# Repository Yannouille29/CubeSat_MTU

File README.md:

# CubeSat MTU

This project is divided into two distinct stages. The first stage involved constructing a CubeSat using the information provided for the AMSAT CubeSatSim prototype, available at [CubeSatSim repository](https://github.com/alanbjohnston/CubeSatSim.git). We followed the steps outlined and replicated the foundation.

The second stage focused on enhancing the CubeSat in various ways to address a specific problem. In our case, we selected two distinct improvements. 

1. **Real-time Visualization of CubeSat in Space using Gyroscope:**
   We developed a 3D visualization of our CubeSat in real-time on a website. This visualization updates dynamically as the ground station receives information.

2. **Prototyping CubeSat Maneuverability using Reaction Wheels:**
   We restructured the CubeSat to accommodate two motors and new electronic circuit components. This enhancement allows the CubeSat to orient itself in space based on reaction wheel principles.

For each of these separate projects, you'll find dedicated folders containing all the necessary information. Additionally, we undertook a thorough analysis of the base code available for CubeSatSim to interact effectively with our enhancements. We've added comments to certain sections of code in the 'soft' directory for the purpose of understanding. It's important to note that these commented code sections have not been altered; they serve merely as tools for comprehension.

## Folder Structure

- **CubeSat_Troubleshooting:** Contains details related to the construction phase following the AMSAT prototype and the solutions to different problems.
- **Visualisation_Improvement:** Includes resources for the real-time 3D visualization of the CubeSat.
- **Reaction_Wheel_Improvement:** Encompasses information regarding the CubeSat's ability to orient itself using reaction wheels.
- **Soft:** Holds the original base code with additional comments for understanding purposes.
- **Web_Serveur:** Contains all the files necessary to visualize various web pages related to the Cubesat, including the work done by other group members.

Please refer to individual folders for specific details and resources related to each stage of the project.

## Important Note

The commented sections in the 'soft' directory serve as aids for understanding the base code and should not be modified. They are solely intended to facilitate comprehension.

## Contributors

- HUGUET Yann(https://github.com/Yannouille29)

Feel free to reach out to us for any inquiries or clarifications regarding this project.

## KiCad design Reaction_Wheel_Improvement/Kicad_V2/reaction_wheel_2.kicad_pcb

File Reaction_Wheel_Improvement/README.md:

# CubeSat Reaction Wheel Project

This repository contains all the essential elements created for the CubeSat Reaction Wheel project.

## Contents

- **3D_Simulation**: This directory contains all the Solidwork files updated specifically for the project. It includes the necessary files for the 3D simulation and modeling related to the CubeSat Reaction Wheel.

- **Arduino**: The Arduino directory houses the code essential for the SparkFun Arduino to operate within the Reaction Wheel project. 

- **KiCad**: This directory comprises the KiCad files, notably the "Kicad_V2" folder. It contains the electronic schema of the project's prototype and offers a potential version that can be translated into a PCB design, taking into account the components used.

## Usage

### 3D_Simulation

This directory includes Solidwork files that are crucial for 3D modeling. To utilize these files:

1. Ensure you have Solidwork installed on your system or another 3D visualisation tool.
2. Open the files using Solidwork to view the 3D model.

### Arduino

The Arduino directory holds the necessary code for the SparkFun Arduino to function within the Reaction Wheel project. Follow these steps:

1. Upload the code to your SparkFun Arduino board.
2. Ensure the connections are set up as specified in the documentation or comments within the code.

### KiCad

In this directory, particularly in the "Kicad_V2" folder, you'll find electronic schemas for the project's prototype and a potential PCB design. To use:

1. Open KiCad and load the schematic files for review or modification.
2. For PCB creation, follow the provided instructions or guidelines for creating a printed circuit board based on the schematic.

## Additional Notes

Please refer to individual directories for specific instructions, codes, or diagrams related to their respective components of the CubeSat Reaction Wheel project.

For questions or inquiries, feel free to contact [Yann HUGUET].

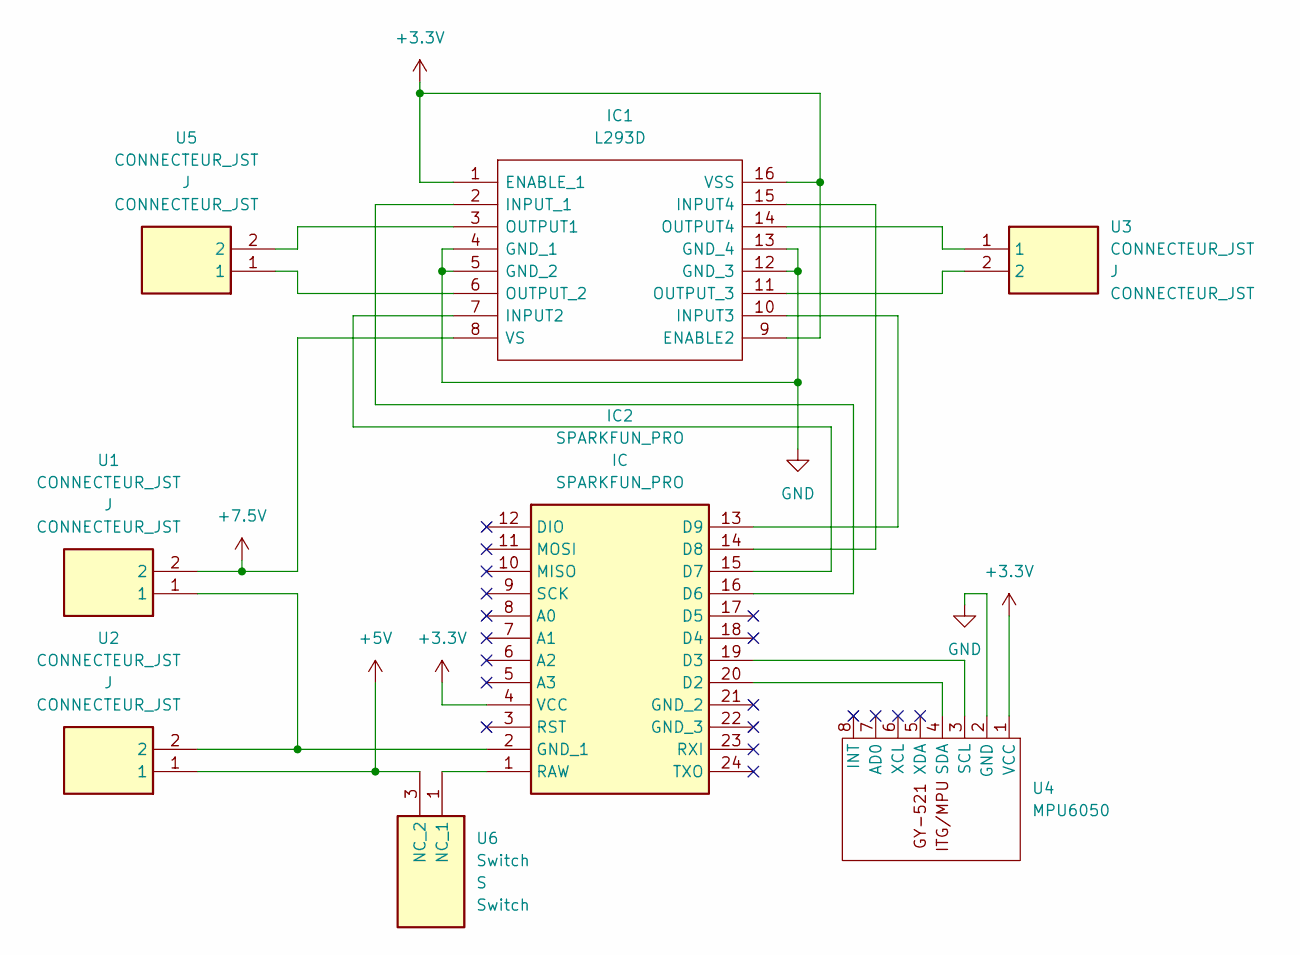
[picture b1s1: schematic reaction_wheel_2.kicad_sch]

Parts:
IC1: L293D; DIP880W50P254L2000H510Q16N; Manufacturer_Part_Number L293D; Mouser Part Number 511-L293D
IC2: SPARKFUN_PRO; DEV12587; Manufacturer_Part_Number DEV-12587; Mouser Part Number 474-DEV-12587
U1, U2, U3, U5: CONNECTEUR_JST; SHDR2W50P0X200_1X2_590X450X600P; Manufacturer_Part_Number B2B-PH-K-S(LF)(SN)
U4: MPU6050
U6: Switch; Manufacturer_Part_Number A11HP; Mouser Part Number 633-A11HP

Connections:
+3.3V: IC1.1 (ENABLE_1), IC1.9 (ENABLE2), IC1.16 (VSS), IC2.4 (VCC), U4.1 (VCC)
+5V: U2.1, U6.3 (NC_2)
+7.5V: IC1.8 (VS), U1.2
GND: IC1.4 (GND_1), IC1.5 (GND_2), IC1.12 (GND_3), IC1.13 (GND_4), U4.2 (GND)
unnamed: IC1.2 (INPUT_1), IC2.16 (D6)
unnamed: IC1.3 (OUTPUT1), U5.2
unnamed: IC1.6 (OUTPUT_2), U5.1
unnamed: IC1.7 (INPUT2), IC2.15 (D7)
unnamed: IC1.10 (INPUT3), IC2.13 (D9)
unnamed: IC1.11 (OUTPUT_3), U3.2
unnamed: IC1.14 (OUTPUT4), U3.1
unnamed: IC1.15 (INPUT4), IC2.14 (D8)
unnamed: IC2.19 (D3), U4.3 (SCL)
unnamed: IC2.2 (GND_1), U1.1, U2.2
unnamed: IC2.20 (D2), U4.4 (SDA)
unnamed: IC2.1 (RAW), U6.1 (NC_1)

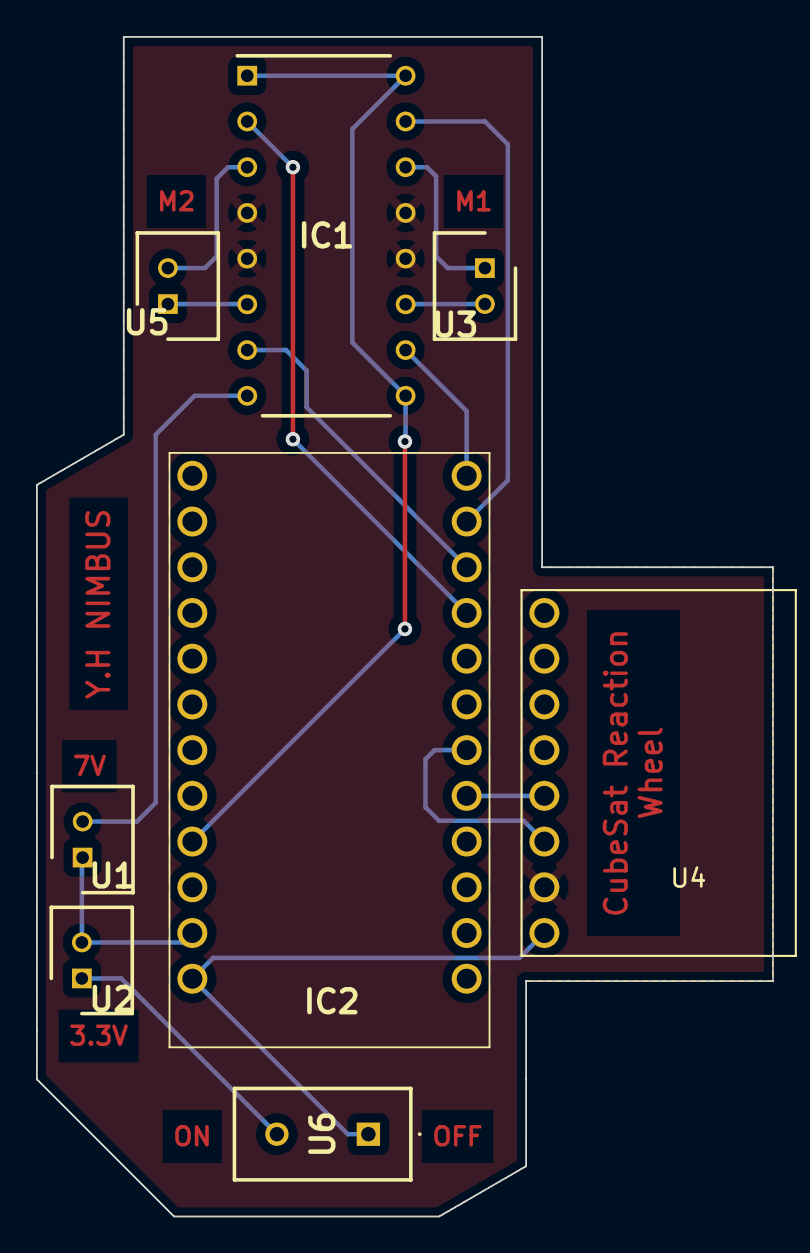
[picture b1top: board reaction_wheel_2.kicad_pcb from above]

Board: 2 copper layers, 40.9 x 65.5 mm, 8 parts (0 on the bottom side), 16 nets.

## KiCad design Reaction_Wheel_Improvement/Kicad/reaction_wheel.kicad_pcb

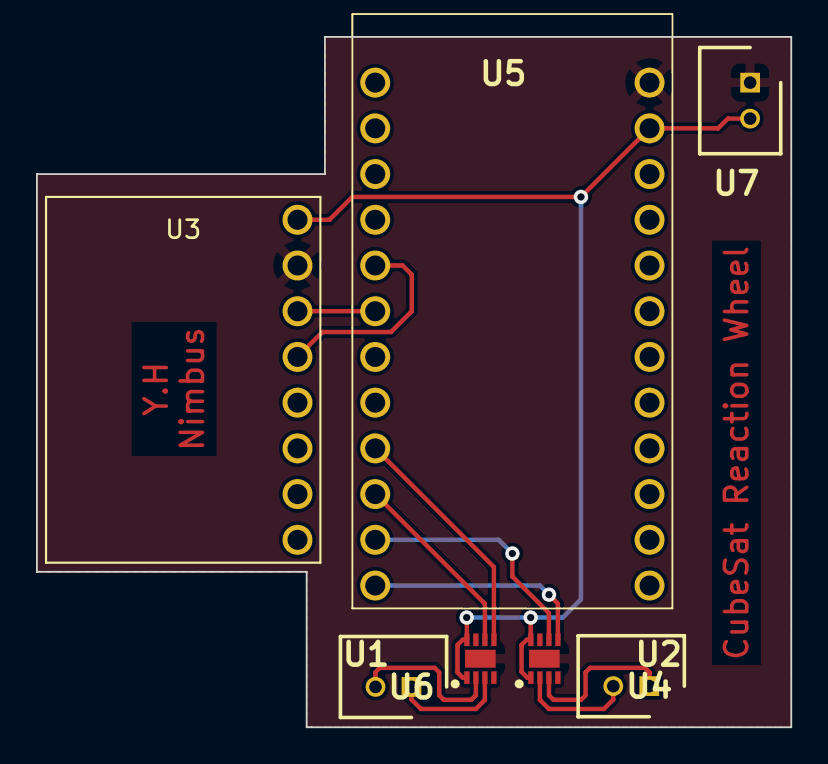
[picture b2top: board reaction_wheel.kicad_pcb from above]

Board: 2 copper layers, 41.9 x 38.4 mm, 7 parts (0 on the bottom side), 12 nets.

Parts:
U1, U2: DRV8838DSGR; SON50P200X200X80-9N
U3: MPU6050
U4, U6, U7: B2B-PH-K-S_LF__SN_; SHDR2W50P0X200_1X2_590X450X600P
U5: DEV-12587; DEV12587

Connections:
+3V3: U1.1 (VIN), U1.8 (VCC), U2.1 (VIN), U2.8 (VCC), U3.1 (VCC), U5.2 (GND_1), U7.2
GND: U1.9 (GND), U2.9 (GND), U3.2 (GND), U5.1 (RAW), U7.1
unnamed: U1.2 (OUT1), U6.2
unnamed: U1.3 (OUT2), U6.1
unnamed: U1.5 (EN), U5.16 (D6)
unnamed: U1.6 (PH), U5.15 (D7)
unnamed: U2.2 (OUT1), U4.2
unnamed: U2.3 (OUT2), U4.1
unnamed: U2.5 (EN), U5.13 (D9)
unnamed: U2.6 (PH), U5.14 (D8)
unnamed: U3.3 (SCL), U5.19 (D3)
unnamed: U3.4 (SDA), U5.20 (D2)

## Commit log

2023-09-18 Addition of modified software code
    The code of the CubeSatSim project but fully commented.
2023-11-20 Update and rename Code_Pi_0.c to Code_Pi_0_Comment.c
    change name
2023-11-20 Update pc.py
    comment
2023-11-20 Update Visu.js
    comment
2023-11-20 Update Test.js
    comment
2023-11-20 Create 2
2023-11-20 Create Processing
2023-11-20 Update Processing
2023-11-20 Create Visu_Cubesat
2023-11-20 Create Modification_Payload
2023-11-20 Create f
2023-11-20 Create l
2023-11-20 Create Gyros_Motor
2023-11-20 Create ll
2023-11-20 Create ff
2023-11-21 Create fefe
2023-11-21 Rename Readme to README.md
2023-11-28 Create llld
2023-11-29 Create fef
2023-11-29 Create efe
2023-11-29 Create ef
2023-11-29 Create dzdz
2023-11-30 Update Visu_Cubesat
